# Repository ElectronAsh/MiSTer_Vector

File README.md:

# MiSTer_Vector
Vector X/Y/Z/R/G/B DAC Board for MiSTer

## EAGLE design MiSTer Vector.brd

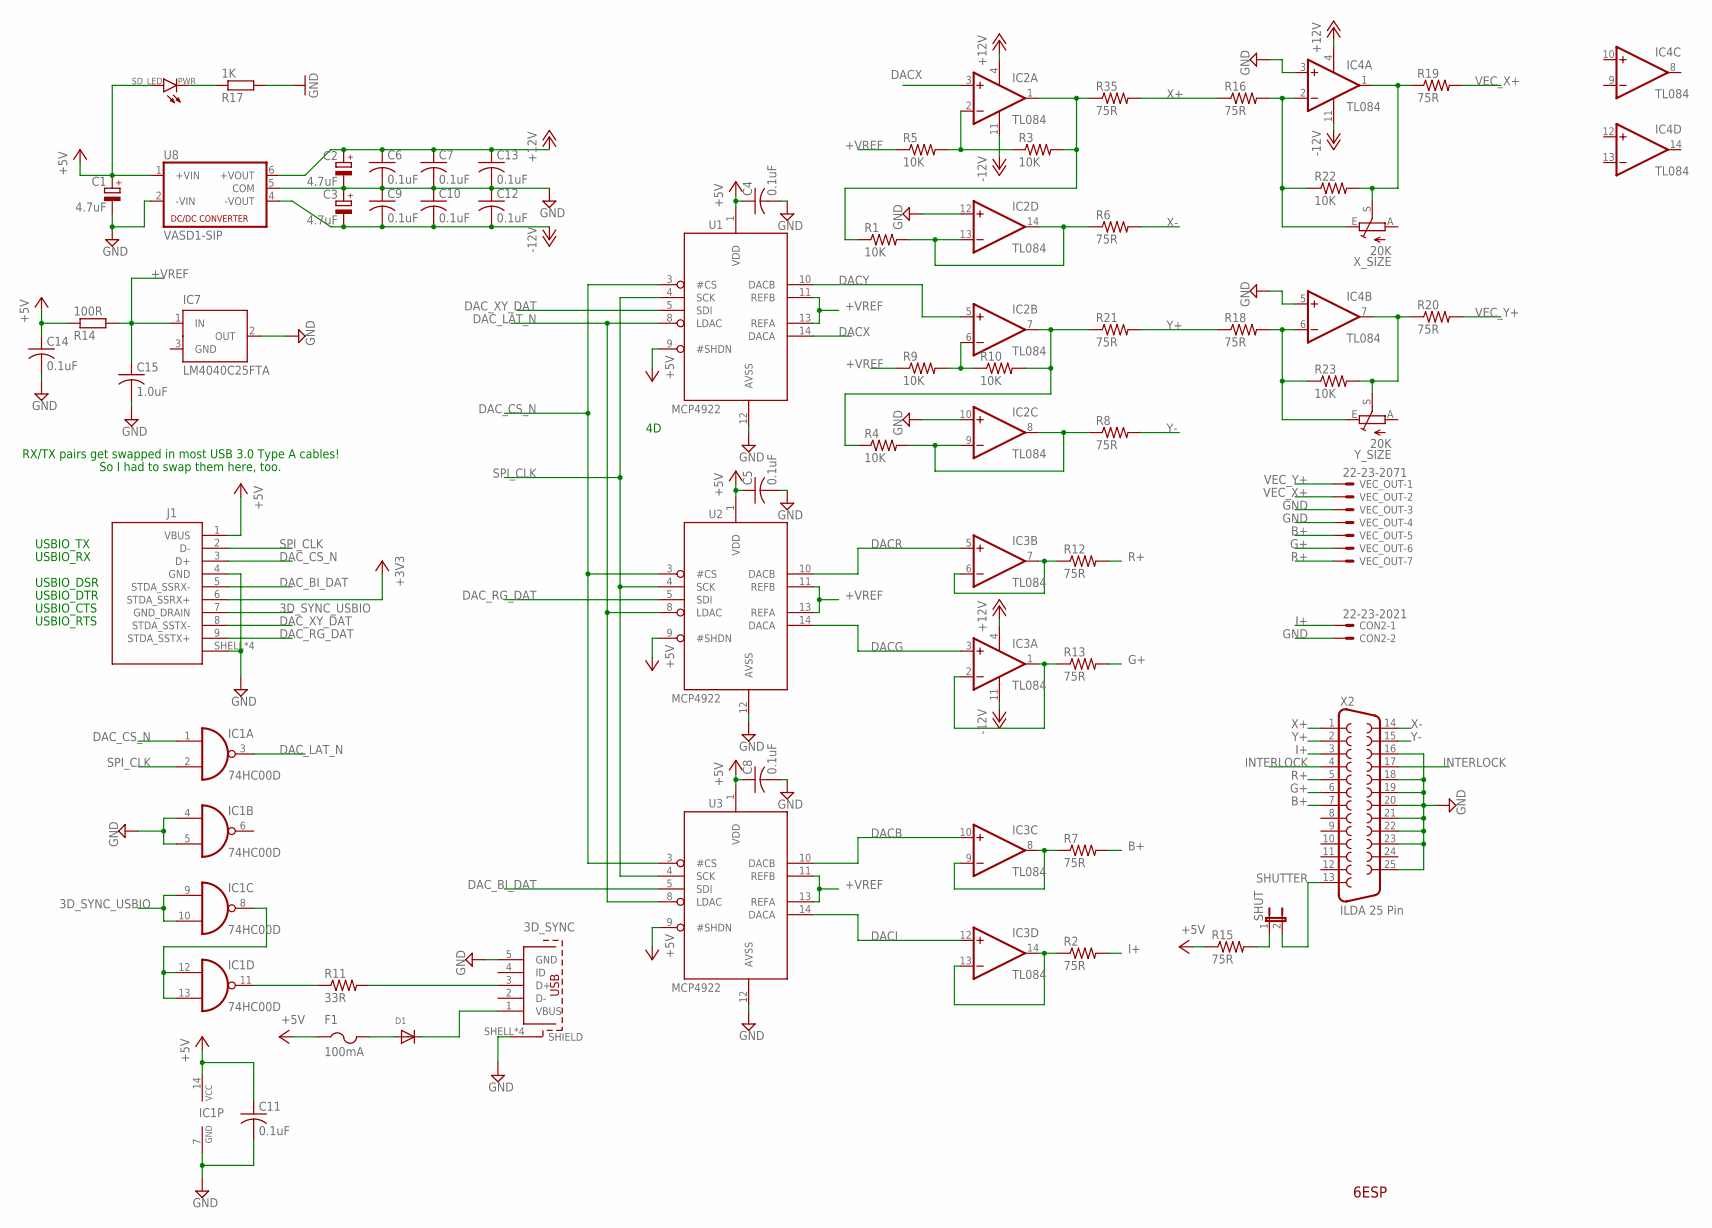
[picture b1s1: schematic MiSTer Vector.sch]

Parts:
3D_SYNC: 65100516121
C1, C2, C3: 4.7uF; CT6032
C4, C5, C6, C7, C8, C9, C10, C11, C12, C13, C14: 0.1uF; C0603
C15: 1.0uF; C0603
CON2: 22-23-2021
D1: DIODESOD-323F; SOD-323F
F1: 100mA; R1206
IC1: 74HC00D; SO14
IC2, IC3, IC4: TL084; SOIC-14
IC7: LM4040C25FTA; SOT23
J1: 692121230100
PWR: SD_LED; 0805_POL
R1, R3, R4, R5, R9, R10, R22, R23: 10K; R0603
R2, R6, R7, R8, R12, R13, R15, R16, R18, R19, R20, R21, R35: 75R; R0603
R11: 33R; R0603
R14: 100R; R0603
R17: 1K; R0603
SHUT: JP1E; JP1
U1, U2, U3: MCP4922; SOIC-14
U8: VASD1-SIP; NMA
VEC_OUT: 22-23-2071
X2: ILDA 25 Pin; F25D
X_SIZE: 20K; B25P
Y_SIZE: 20K; B25P

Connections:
3D_SYNC_USBIO: IC1.9 (I0), IC1.10 (I1), J1.7 (GND_DRAIN)
+3V3: J1.6 (STDA_SSRX+)
+5V: C1.+, C4.1, C5.1, C8.1, C11.1, C14.1, F1.1, IC1.14 (VCC), J1.1 (VBUS), PWR.+ (A), R14.1, R15.1, U1.1 (VDD), U1.9 (#SHDN), U2.1 (VDD), U2.9 (#SHDN), U3.1 (VDD), U3.9 (#SHDN), U8.1 (+VIN)
+12V: C2.+, C6.1, C7.1, C13.1, IC2.4 (V+), IC3.4 (V+), IC4.4 (V+), U8.6 (+VOUT)
+VREF: C15.1, IC7.1 (IN), R5.1, R9.1, R14.2, U1.11 (REFB), U1.13 (REFA), U2.11 (REFB), U2.13 (REFA), U3.11 (REFB), U3.13 (REFA)
-12V: C3.-, C9.2, C10.2, C12.2, IC2.11 (V-), IC3.11 (V-), IC4.11 (V-), U8.4 (-VOUT)
B1+: IC3.8 (OUT), IC3.9 (-IN), R7.1
B+: R7.2, VEC_OUT.5, X2.7
DACB: IC3.10 (+IN), U3.10 (DACB)
DACG: IC3.3 (+IN), U2.14 (DACA)
DACI: IC3.12 (+IN), U3.14 (DACA)
DACR: IC3.5 (+IN), U2.10 (DACB)
DACX: IC2.3 (+IN), U1.14 (DACA)
DACY: IC2.5 (+IN), U1.10 (DACB)
DAC_BI_DAT: J1.5 (STDA_SSRX-), U3.5 (SDI)
DAC_CS_N: IC1.1 (I0), J1.3 (D+), U1.3 (#CS), U2.3 (#CS), U3.3 (#CS)
DAC_LAT_N: IC1.3 (O), U1.8 (LDAC), U2.8 (LDAC), U3.8 (LDAC)
DAC_RG_DAT: J1.9 (STDA_SSTX+), U2.5 (SDI)
DAC_XY_DAT: J1.8 (STDA_SSTX-), U1.5 (SDI)
G1+: IC3.1 (OUT), IC3.2 (-IN), R13.1
G+: R13.2, VEC_OUT.6, X2.6
GND: 3D_SYNC.5 (GND), 3D_SYNC.SHELL (SHIELD), 3D_SYNC.SHELL1 (SHIELD), 3D_SYNC.SHELL2 (SHIELD), 3D_SYNC.SHELL3 (SHIELD), C1.-, C2.-, C3.+, C4.2, C5.2, C6.2, C7.2, C8.2, C9.1, C10.1, C11.2, C12.1, C13.2, C14.2, C15.2, CON2.2, IC1.4 (I0), IC1.5 (I1), IC1.7 (GND), IC2.10 (+IN), IC2.12 (+IN), IC4.3 (+IN), IC4.5 (+IN), IC7.2 (OUT), IC7.3 (GND), J1.4 (GND), J1.SHELL (SHIELD), J1.SHELL1 (SHIELD), J1.SHELL2 (SHIELD), J1.SHELL3 (SHIELD), R17.2, U1.12 (AVSS), U2.12 (AVSS), U3.12 (AVSS), U8.2 (-VIN), U8.5 (COM), VEC_OUT.3, VEC_OUT.4, X2.16, X2.18, X2.19, X2.20, X2.21, X2.22, X2.23, X2.25
I1+: IC3.13 (-IN), IC3.14 (OUT), R2.1
I+: CON2.1, R2.2, X2.3
INTERLOCK: X2.4, X2.17
unnamed: IC2.1 (OUT), R1.1, R3.2, R35.1
unnamed: IC2.7 (OUT), R4.1, R10.2, R21.1
unnamed: IC2.6 (-IN), R9.2, R10.1
unnamed: IC2.8 (OUT), IC2.9 (-IN), R4.2, R8.1
unnamed: IC2.13 (-IN), IC2.14 (OUT), R1.2, R6.1
unnamed: 3D_SYNC.1 (VBUS), D1.C
unnamed: IC1.11 (O), R11.1
unnamed: IC1.8 (O), IC1.12 (I0), IC1.13 (I1)
unnamed: 3D_SYNC.3 (D+), R11.2
unnamed: PWR.- (C), R17.1
unnamed: D1.A, F1.2
unnamed: R15.2, SHUT.1
unnamed: IC4.2 (-IN), R16.2, R22.1, X_SIZE.E
unnamed: IC4.6 (-IN), R18.2, R23.1, Y_SIZE.E
unnamed: IC4.7 (OUT), R20.1, R23.2, Y_SIZE.S
unnamed: IC4.1 (OUT), R19.1, R22.2, X_SIZE.S
unnamed: IC2.2 (-IN), R3.1, R5.2
R1+: IC3.6 (-IN), IC3.7 (OUT), R12.1
R+: R12.2, VEC_OUT.7, X2.5
SHUTTER: SHUT.2, X2.13
SPI_CLK: IC1.2 (I1), J1.2 (D-), U1.4 (SCK), U2.4 (SCK), U3.4 (SCK)
VEC_X+: R19.2, VEC_OUT.2
VEC_Y+: R20.2, VEC_OUT.1
X+: R16.1, R35.2, X2.1
X-: R6.2, X2.14
Y+: R18.1, R21.2, X2.2
Y-: R8.2, X2.15

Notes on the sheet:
6ESP
USBIO_TX
USBIO_RX
USBIO_DSR
USBIO_DTR
USBIO_CTS
USBIO_RTS
RX/TX pairs get swapped in most USB 3.0 Type A cables!
So I had to swap them here, too.

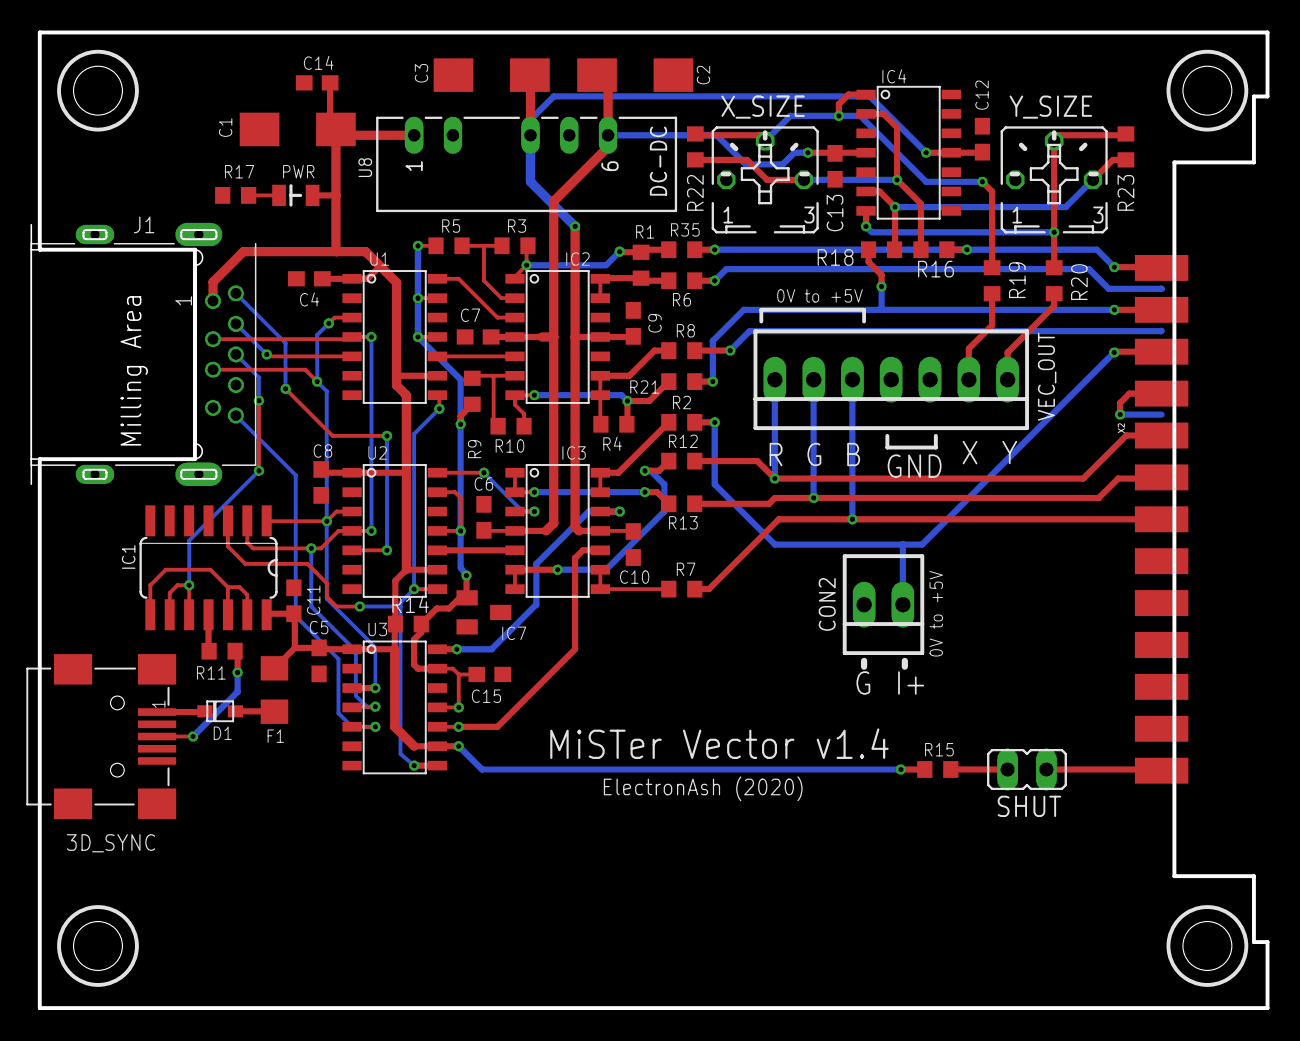
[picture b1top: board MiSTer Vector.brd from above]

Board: 2 copper layers, 80.9 x 63.9 mm, 59 parts (0 on the bottom side), 51 nets.

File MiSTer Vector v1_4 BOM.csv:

"Part";"Value";"Device";"Package";"Description";"MF";"MPN";"OC_FARNELL";"OC_NEWARK";
"3D_SYNC";"";"65100516121";"65100516121";"WR-COM SMT Horizontal 5 Contacts Mini USB Typ B=>Code : Con_I-O_COM_MiniUSB_65100516121";"";"";"";"";
"C1";"4.7uF";"CPOL-EUCT6032";"CT6032";"POLARIZED CAPACITOR, European symbol";"";"";"";"";
"C2";"4.7uF";"CPOL-EUCT6032";"CT6032";"POLARIZED CAPACITOR, European symbol";"";"";"";"";
"C3";"4.7uF";"CPOL-EUCT6032";"CT6032";"POLARIZED CAPACITOR, European symbol";"";"";"";"";
"C4";"0.1uF";"C-USC0603";"C0603";"CAPACITOR, American symbol";"";"";"";"";
"C5";"0.1uF";"C-USC0603";"C0603";"CAPACITOR, American symbol";"";"";"";"";
"C6";"0.1uF";"C-USC0603";"C0603";"CAPACITOR, American symbol";"";"";"";"";
"C7";"0.1uF";"C-USC0603";"C0603";"CAPACITOR, American symbol";"";"";"";"";
"C8";"0.1uF";"C-USC0603";"C0603";"CAPACITOR, American symbol";"";"";"";"";
"C9";"0.1uF";"C-USC0603";"C0603";"CAPACITOR, American symbol";"";"";"";"";
"C10";"0.1uF";"C-USC0603";"C0603";"CAPACITOR, American symbol";"";"";"";"";
"C11";"0.1uF";"C-USC0603";"C0603";"CAPACITOR, American symbol";"";"";"";"";
"C12";"0.1uF";"C-USC0603";"C0603";"CAPACITOR, American symbol";"";"";"";"";
"C13";"0.1uF";"C-USC0603";"C0603";"CAPACITOR, American symbol";"";"";"";"";
"C14";"0.1uF";"C-USC0603";"C0603";"CAPACITOR, American symbol";"";"";"";"";
"C15";"1.0uF";"C-USC0603";"C0603";"CAPACITOR, American symbol";"";"";"";"";
"CON2";"22-23-2021";"22-23-2021";"22-23-2021";".100" (2.54mm) Center Header - 2 Pin";"MOLEX";"22-23-2021";"1462926";"25C3832";
"D1";"";"DIODESOD-323F";"SOD-323F";"Diode";"";"";"";"";
"F1";"100mA";"PTCFUSE-1206";"R1206";"PTC fuses, resettable thermistors";"";"";"";"";
"IC1";"74HC00D";"74HC00D";"SO14";"Quad 2-input NAND gate";"";"";"";"";
"IC2";"TL084";"TL084";"SOIC-14";"Texas Instruments TL084 JFET General Purpose Op-Amp";"";"";"";"";
"IC3";"TL084";"TL084";"SOIC-14";"Texas Instruments TL084 JFET General Purpose Op-Amp";"";"";"";"";
"IC4";"TL084";"TL084";"SOIC-14";"Texas Instruments TL084 JFET General Purpose Op-Amp";"";"";"";"";
"IC7";"LM4040C25FTA";"MAX6520";"SOT23";"1.2V Voltage Reference 50ppm/°C, SOT23, 3-Terminal";"MAXIM";"MAX6520EUR-T";"unknown";"02J4586";
"J1";"";"692121230100";"692121230100";"WR-COM - USB 3.0 HORIZONTAL TYPE A";"";"";"";"";
"PWR";"SD_LED";"LED0805";"0805_POL";"LED";"";"";"";"";
"R1";"10K";"R-US_R0603";"R0603";"RESISTOR, American symbol";"";"";"";"";
"R2";"75R";"R-US_R0603";"R0603";"RESISTOR, American symbol";"";"";"";"";
"R3";"10K";"R-US_R0603";"R0603";"RESISTOR, American symbol";"";"";"";"";
"R4";"10K";"R-US_R0603";"R0603";"RESISTOR, American symbol";"";"";"";"";
"R5";"10K";"R-US_R0603";"R0603";"RESISTOR, American symbol";"";"";"";"";
"R6";"75R";"R-US_R0603";"R0603";"RESISTOR, American symbol";"";"";"";"";
"R7";"75R";"R-US_R0603";"R0603";"RESISTOR, American symbol";"";"";"";"";
"R8";"75R";"R-US_R0603";"R0603";"RESISTOR, American symbol";"";"";"";"";
"R9";"10K";"R-US_R0603";"R0603";"RESISTOR, American symbol";"";"";"";"";
"R10";"10K";"R-US_R0603";"R0603";"RESISTOR, American symbol";"";"";"";"";
"R11";"33R";"R-US_R0603";"R0603";"RESISTOR, American symbol";"";"";"";"";
"R12";"75R";"R-US_R0603";"R0603";"RESISTOR, American symbol";"";"";"";"";
"R13";"75R";"R-US_R0603";"R0603";"RESISTOR, American symbol";"";"";"";"";
"R14";"100R";"R-EU_R0603";"R0603";"RESISTOR, European symbol";"";"";"";"";
"R15";"75R";"R-US_R0603";"R0603";"RESISTOR, American symbol";"";"";"";"";
"R16";"75R";"R-US_R0603";"R0603";"RESISTOR, American symbol";"";"";"";"";
"R17";"1K";"R-EU_R0603";"R0603";"RESISTOR, European symbol";"";"";"";"";
"R18";"75R";"R-US_R0603";"R0603";"RESISTOR, American symbol";"";"";"";"";
"R19";"75R";"R-US_R0603";"R0603";"RESISTOR, American symbol";"";"";"";"";
"R20";"75R";"R-US_R0603";"R0603";"RESISTOR, American symbol";"";"";"";"";
"R21";"75R";"R-US_R0603";"R0603";"RESISTOR, American symbol";"";"";"";"";
"R22";"10K";"R-US_R0603";"R0603";"RESISTOR, American symbol";"";"";"";"";
"R23";"10K";"R-US_R0603";"R0603";"RESISTOR, American symbol";"";"";"";"";
"R35";"75R";"R-US_R0603";"R0603";"RESISTOR, American symbol";"";"";"";"";
"SHUT";"";"JP1E";"JP1";"JUMPER";"";"";"";"";
"U1";"MCP4922";"MCP4922";"SOIC-14";"";"";"";"";"";
"U2";"MCP4922";"MCP4922";"SOIC-14";"";"";"";"";"";
"U3";"MCP4922";"MCP4922";"SOIC-14";"";"";"";"";"";
"U8";"VASD1-SIP";"NMA";"NMA";"DC-DC CONVERTER";"C & D TECHNOLOGIES, INC";"NMA0515SC";"1021434";"61K3064";
"VEC_OUT";"22-23-2071";"22-23-2071";"22-23-2071";".100" (2.54mm) Center Header - 7 Pin";"MOLEX";"22-23-2071";"1654534";"56H0445";
"X2";"ILDA 25 Pin";"F25D";"F25D";"D-SUB 25";"";"";"";"";
"X_SIZE";"20K";"TRIM_EU-B25P";"B25P";"POTENTIOMETER";"";"";"";"";
"Y_SIZE";"20K";"TRIM_EU-B25P";"B25P";"POTENTIOMETER";"";"";"";"";

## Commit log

2020-01-03 hook up DE15 pins 6,7,8 to Gnd
2020-01-05 driving the DAC chips in parallel now, because FPGAs rule
2020-01-09 added 3-pin VESA miniDIN, for 3D glasses
2020-01-09 swapped two USBIO pins, for better signal integrity
2020-01-09 changed DB15 to DB25, for use with laser projectors
2020-01-09 made the PCB longer, to fit a specific project box
2020-01-10 changed the miniDIN for a miniUSB, to fit the case
2020-01-10 added BOM csv
2020-01-10 added VREF adj switch and pot, plus ILDA shutter jumper
2020-01-12 added size adjustment for Molex output. ILDA fixed to 0-5V
2020-01-31 swapped USBIO TX/RX pairs, as done in most USB3 TypeA-TypeA cables
2020-01-31 routed the swapped TX/RX pairs on USBIO
2020-04-29 Add the BOM for the v1.4 DAC board.

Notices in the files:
parts and their libraries:
632723100011_Eagle_WR-USB_rev19b: Copyright: Würth Elektronik
